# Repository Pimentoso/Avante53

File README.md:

# Avante53
Open-source 53 keys alice-style ortho keyboard. Features hotswap switches, a rotary encoder, and OLED screen.

## Bill of materials
- 53 Hotswap sockets
  - https://www.aliexpress.com/item/4001051840976.html
- 54 SMD 1N4148 diodes
  - https://www.aliexpress.com/item/32849879904.html
- Teensy 2.0 microcontroller
  - https://www.aliexpress.com/item/4000829915634.html
- a rotary encoder
  - https://www.aliexpress.com/item/10000056483250.html (the 15mm half handle)
- 11x 5mm m2 standoffs
  - https://www.aliexpress.com/item/1005004564012666.html
- 11x m2 nuts
- 11x short m2 screws (8-10mm)
- 53 switches of your choice
- any set of preonic/ortho keycaps
  - I used https://www.aliexpress.com/item/1005003294964787.html
- recommended: a 3d printer for the case and plate
- optional: 128x32 OLED screen breakout board
  - https://www.aliexpress.com/item/32850288143.html
- optional: a very short ws2812b led strip (like 5 leds)
  - https://www.aliexpress.com/item/2036819167.html

## Building
It's pretty straightforward.
- get the PCB printed at JLCPCB or your supplier of choice.
- solder the teensy on the underside with its header pins.
- solder the diodes and hotswap sockets.
- solder the encoder and oled screen on the top side of the board.
- print the case, and punch open the screw holes. If you printed the 2 separate pieces, put them on a flat surface like glass, and glue them together with super glue.
- push the nuts in the holes from the bottom, and screw in the standoffs.
- put the PCB in the case and screw it in.
- print the plate and install it along with the switches.
- done!

## Flashing
You can clone my fork of vial (https://github.com/Pimentoso/vial-qmk) and compile the keymap for this keyboard with `make pimentoso/avante53:vial`
Or you can just flash the compiled binary you can find in the `firmware` folder, using QMK toolbox or a tool of your choice.
Then you can use vial to edit the keymap.

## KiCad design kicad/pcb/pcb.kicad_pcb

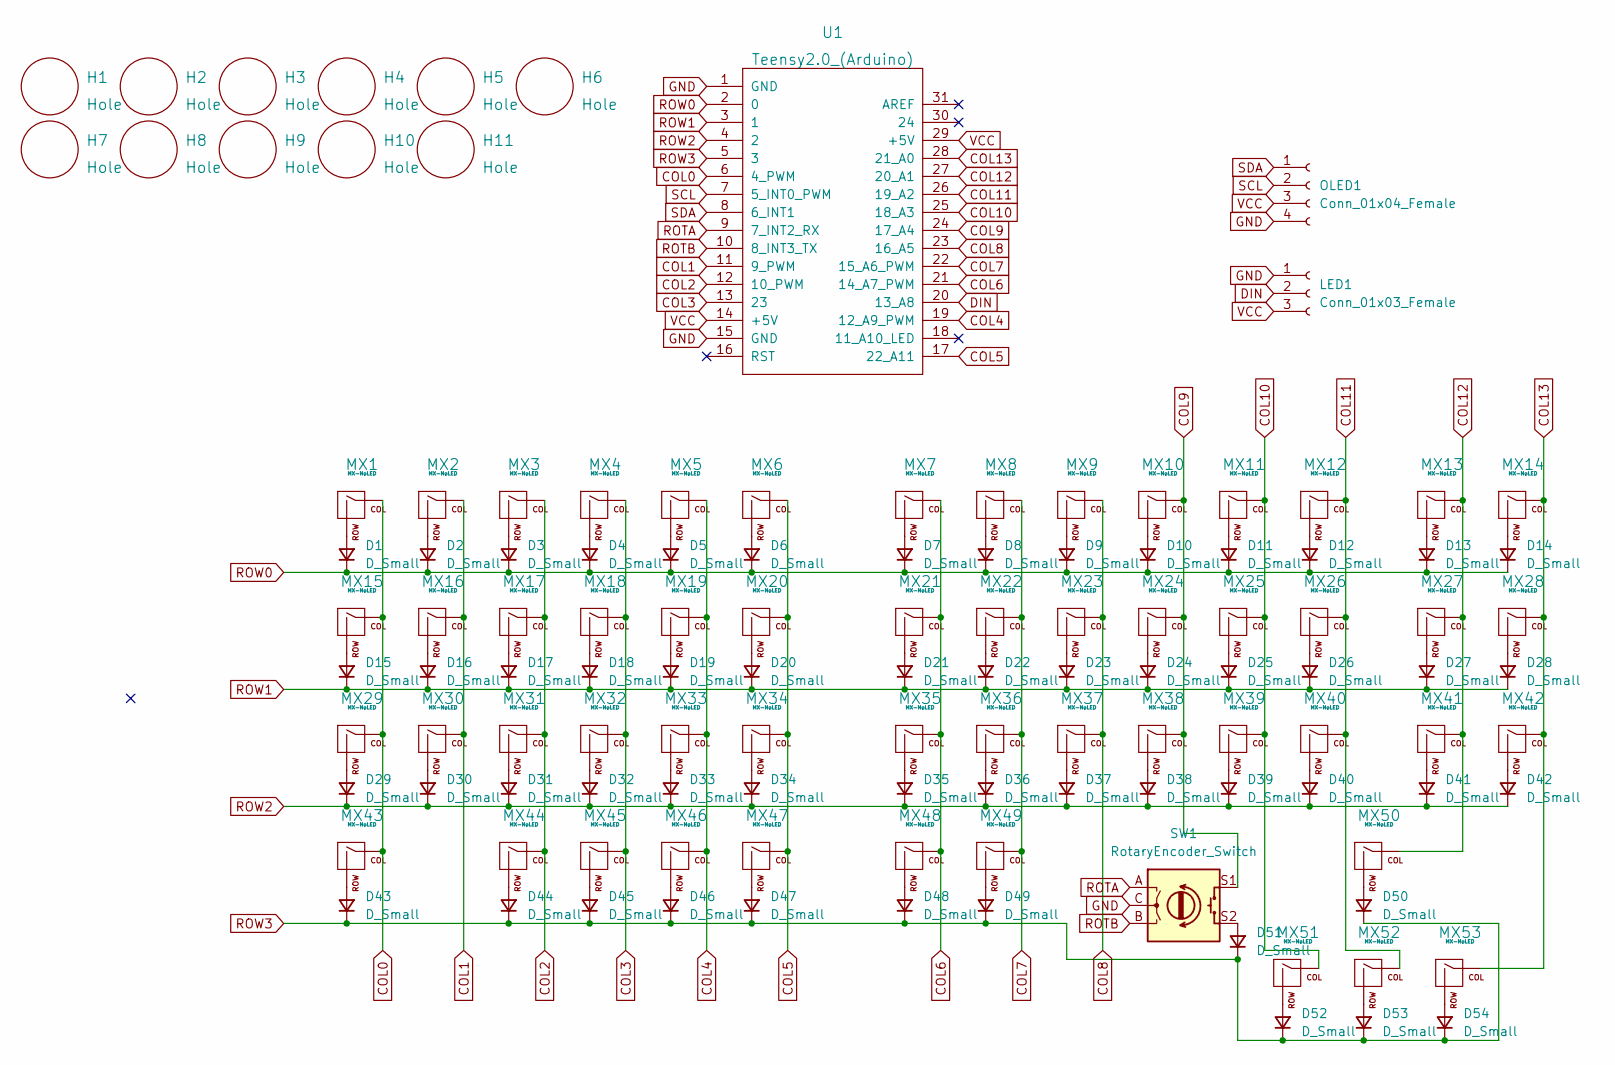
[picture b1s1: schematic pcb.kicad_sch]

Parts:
D1, D2, D3, D4, D5, D6, D7, D8, D9, D10, D11, D12, D13, D14, D15, D16, D17, D18, D19, D20, D21, D22, D23, D24, D25, D26, D27, D28, D29, D30, D31, D32, D33, D34, D35, D36, D37, D38, D39, D40, D41, D42, D43, D44, D45, D46, D47, D48, D49, D50, D51, D52, D53, D54: D_Small; D_MiniMELF
H1, H2, H3, H4, H5, H6, H7, H8, H9, H10, H11: Hole; MountingHole_2.2mm_M2_Pad_TopOnly
LED1: Conn_01x03_Female; PinHeader_1x03_P2.54mm_Vertical
MX1, MX2, MX3, MX4, MX5, MX6, MX7, MX8, MX9, MX10, MX11, MX12, MX13, MX14, MX15, MX16, MX17, MX18, MX19, MX20, MX21, MX22, MX23, MX24, MX25, MX26, MX27, MX28, MX29, MX30, MX31, MX32, MX33, MX34, MX35, MX36, MX37, MX38, MX39, MX40, MX41, MX42, MX43, MX44, MX45, MX46, MX47, MX48, MX49, MX50, MX51, MX52, MX53: MX-NoLED; MXOnly-1U-Hotswap
OLED1: Conn_01x04_Female; PinHeader_1x04_P2.54mm_Vertical
SW1: RotaryEncoder_Switch; RotaryEncoder_EC11
U1: Teensy2.0_(Arduino); Teensy_2.0

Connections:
COL0: MX1.1 (COL), MX15.1 (COL), MX29.1 (COL), MX43.1 (COL), U1.6 (4_PWM)
COL1: MX2.1 (COL), MX16.1 (COL), MX30.1 (COL), U1.11 (9_PWM)
COL2: MX3.1 (COL), MX17.1 (COL), MX31.1 (COL), MX44.1 (COL), U1.12 (10_PWM)
COL3: MX4.1 (COL), MX18.1 (COL), MX32.1 (COL), MX45.1 (COL), U1.13 (23)
COL4: MX5.1 (COL), MX19.1 (COL), MX33.1 (COL), MX46.1 (COL), U1.19 (12_A9_PWM)
COL5: MX6.1 (COL), MX20.1 (COL), MX34.1 (COL), MX47.1 (COL), U1.17 (22_A11)
COL6: MX7.1 (COL), MX21.1 (COL), MX35.1 (COL), MX48.1 (COL), U1.21 (14_A7_PWM)
COL7: MX8.1 (COL), MX22.1 (COL), MX36.1 (COL), MX49.1 (COL), U1.22 (15_A6_PWM)
COL8: MX9.1 (COL), MX23.1 (COL), MX37.1 (COL), U1.23 (16_A5)
COL9: MX10.1 (COL), MX24.1 (COL), MX38.1 (COL), SW1.S1, U1.24 (17_A4)
COL10: MX11.1 (COL), MX25.1 (COL), MX39.1 (COL), MX51.1 (COL), U1.25 (18_A3)
COL11: MX12.1 (COL), MX26.1 (COL), MX40.1 (COL), MX52.1 (COL), U1.26 (19_A2)
COL12: MX13.1 (COL), MX27.1 (COL), MX41.1 (COL), MX50.1 (COL), U1.27 (20_A1)
COL13: MX14.1 (COL), MX28.1 (COL), MX42.1 (COL), MX53.1 (COL), U1.28 (21_A0)
DIN: LED1.2, U1.20 (13_A8)
GND: LED1.1, OLED1.4, SW1.C, U1.1 (GND), U1.15 (GND)
unnamed: D1.2 (A), MX1.2 (ROW)
unnamed: D2.2 (A), MX2.2 (ROW)
unnamed: D3.2 (A), MX3.2 (ROW)
unnamed: D4.2 (A), MX4.2 (ROW)
unnamed: D5.2 (A), MX5.2 (ROW)
unnamed: D6.2 (A), MX6.2 (ROW)
unnamed: D7.2 (A), MX7.2 (ROW)
unnamed: D8.2 (A), MX8.2 (ROW)
unnamed: D9.2 (A), MX9.2 (ROW)
unnamed: D10.2 (A), MX10.2 (ROW)
unnamed: D11.2 (A), MX11.2 (ROW)
unnamed: D12.2 (A), MX12.2 (ROW)
unnamed: D13.2 (A), MX13.2 (ROW)
unnamed: D14.2 (A), MX14.2 (ROW)
unnamed: D15.2 (A), MX15.2 (ROW)
unnamed: D16.2 (A), MX16.2 (ROW)
unnamed: D17.2 (A), MX17.2 (ROW)
unnamed: D18.2 (A), MX18.2 (ROW)
unnamed: D19.2 (A), MX19.2 (ROW)
unnamed: D20.2 (A), MX20.2 (ROW)
unnamed: D21.2 (A), MX21.2 (ROW)
unnamed: D22.2 (A), MX22.2 (ROW)
unnamed: D23.2 (A), MX23.2 (ROW)
unnamed: D24.2 (A), MX24.2 (ROW)
unnamed: D25.2 (A), MX25.2 (ROW)
unnamed: D26.2 (A), MX26.2 (ROW)
unnamed: D27.2 (A), MX27.2 (ROW)
unnamed: D28.2 (A), MX28.2 (ROW)
unnamed: D29.2 (A), MX29.2 (ROW)
unnamed: D30.2 (A), MX30.2 (ROW)
unnamed: D31.2 (A), MX31.2 (ROW)
unnamed: D32.2 (A), MX32.2 (ROW)
unnamed: D33.2 (A), MX33.2 (ROW)
unnamed: D34.2 (A), MX34.2 (ROW)
unnamed: D35.2 (A), MX35.2 (ROW)
unnamed: D36.2 (A), MX36.2 (ROW)
unnamed: D37.2 (A), MX37.2 (ROW)
unnamed: D38.2 (A), MX38.2 (ROW)
unnamed: D39.2 (A), MX39.2 (ROW)
unnamed: D40.2 (A), MX40.2 (ROW)
unnamed: D41.2 (A), MX41.2 (ROW)
unnamed: D42.2 (A), MX42.2 (ROW)
unnamed: D43.2 (A), MX43.2 (ROW)
unnamed: D44.2 (A), MX44.2 (ROW)
unnamed: D45.2 (A), MX45.2 (ROW)
unnamed: D46.2 (A), MX46.2 (ROW)
unnamed: D47.2 (A), MX47.2 (ROW)
unnamed: D48.2 (A), MX48.2 (ROW)
unnamed: D49.2 (A), MX49.2 (ROW)
unnamed: D50.2 (A), MX50.2 (ROW)
unnamed: D51.2 (A), SW1.S2
unnamed: D52.2 (A), MX51.2 (ROW)
unnamed: D53.2 (A), MX52.2 (ROW)
unnamed: D54.2 (A), MX53.2 (ROW)
ROTA: SW1.A, U1.9 (7_INT2_RX)
ROTB: SW1.B, U1.10 (8_INT3_TX)
ROW0: D1.1 (K), D2.1 (K), D3.1 (K), D4.1 (K), D5.1 (K), D6.1 (K), D7.1 (K), D8.1 (K), D9.1 (K), D10.1 (K), D11.1 (K), D12.1 (K), D13.1 (K), D14.1 (K), U1.2 (0)
ROW1: D15.1 (K), D16.1 (K), D17.1 (K), D18.1 (K), D19.1 (K), D20.1 (K), D21.1 (K), D22.1 (K), D23.1 (K), D24.1 (K), D25.1 (K), D26.1 (K), D27.1 (K), D28.1 (K), U1.3 (1)
ROW2: D29.1 (K), D30.1 (K), D31.1 (K), D32.1 (K), D33.1 (K), D34.1 (K), D35.1 (K), D36.1 (K), D37.1 (K), D38.1 (K), D39.1 (K), D40.1 (K), D41.1 (K), D42.1 (K), U1.4 (2)
ROW3: D43.1 (K), D44.1 (K), D45.1 (K), D46.1 (K), D47.1 (K), D48.1 (K), D49.1 (K), D50.1 (K), D51.1 (K), D52.1 (K), D53.1 (K), D54.1 (K), U1.5 (3)
SCL: OLED1.2, U1.7 (5_INT0_PWM)
SDA: OLED1.1, U1.8 (6_INT1)
VCC: LED1.3, OLED1.3, U1.14 (+5V), U1.29 (+5V)

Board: 2 copper layers, 122 parts (1 on the bottom side), 79 nets, no tracks yet.

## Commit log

2024-01-31 edits before formatting mac
